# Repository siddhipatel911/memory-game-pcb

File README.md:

# Memory Game Revision - PCB Design

A custom ESP32-based memory game built on a hand-designed PCB.  
This is a learning project covering embedded firmware, schematic design, and PCB layout.

> **PCB prototype sponsored by [PCBWay](https://www.pcbway.com)**

---

## Project Status

| Stage | Status |
|-------|--------|
| Breadboard prototype | ✅ Complete |
| Hardware test firmware | ✅ Complete |
| KiCad schematic | ✅ Complete |
| PCB layout | ✅ Complete |
| PCB manufacturing | 🔄 In progress (PCBWay) |
| Final game logic firmware | ⏳ Planned |

---

## Related Project

This repository is a simplified hardware redesign of the original Delirium Memory Game project.

The original project focused on a more advanced **RGB** memory game system with expanded gameplay logic and additional hardware features.

This repository focuses specifically on:

- **ESP32** hardware prototyping
- KiCad **PCB** design
- breadboard testing
- **PCB** manufacturing preparation
- beginner-friendly embedded hardware development

Original project repository:

➡️ [https://github.com/siddhipatel911/Delirium-Memory-Game](https://github.com/siddhipatel911/Delirium-Memory-Game)

---

## Hardware Overview

- **Microcontroller:** ESP32-WROOM-32E dev board (removable via female socket headers)
- **Inputs:** 3 tactile pushbuttons (GPIO 21, 22, 23)
- **Outputs:** 3 LEDs with 220Ω current-limiting resistors (GPIO 25, 26, 27)
- **PCB:** Custom 2-layer board designed in KiCad 10, manufactured by PCBWay
- **Power:** USB via ESP32 dev board

### GPIO Mapping

| Component | GPIO |
|-----------|------|
| SW1 | 23 |
| SW2 | 22 |
| SW3 | 21 |
| D1 | 25 |
| D2 | 26 |
| D3 | 27 |

---

## PCB Design

Designed in **KiCad 10.0.0**. 2-layer FR4 board, 82.5 × 62.2mm.

- All through-hole components for beginner-friendly hand soldering
- Female socket headers allow the ESP32 dev board to remain removable and reusable
- F.Cu GND copper pour
- 4× M3 mounting holes at corners

### Schematic

### PCB Layout

### 3D Render

---

## Breadboard Prototype

Initial hardware validation was done on a breadboard before PCB design.

---

## Firmware

### Current: Hardware Test
Located in [`memory_game/firmware/hardware_test/`](memory_game/firmware/hardware_test/)

Tests button inputs and LED outputs — each button lights its corresponding LED when pressed.

### Planned: Game Logic
The final memory game firmware will be added to [`memory_game/firmware/game_logic/`](memory_game/firmware/game_logic/) after hardware is validated.

---

## Repository Structure

```text
memory-game-pcb/
└── memory_game/
    ├── firmware/
    │   ├── hardware_test/     # Current test firmware
    │   └── game_logic/        # Final game firmware (coming soon)
    ├── hardware/
    │   ├── kicad/             # KiCad schematic and PCB files
    │   └── gerbers/           # Gerber files for manufacturing
    ├── docs/
    │   └── images/            # Project photos and renders
    └── bom/
        └── bom.md             # Bill of materials
```

---

## Sponsor

PCB prototypes for this project are sponsored by **[PCBWay](https://www.pcbway.com)**.  
- PCBWay provides high-quality PCB manufacturing and assembly services for makers, hobbyists, and professionals.  
- I'll be sharing my honest review of the manufacturing quality and experience once the boards arrive.

---

## License

MIT License — see [LICENSE](LICENSE) for details.

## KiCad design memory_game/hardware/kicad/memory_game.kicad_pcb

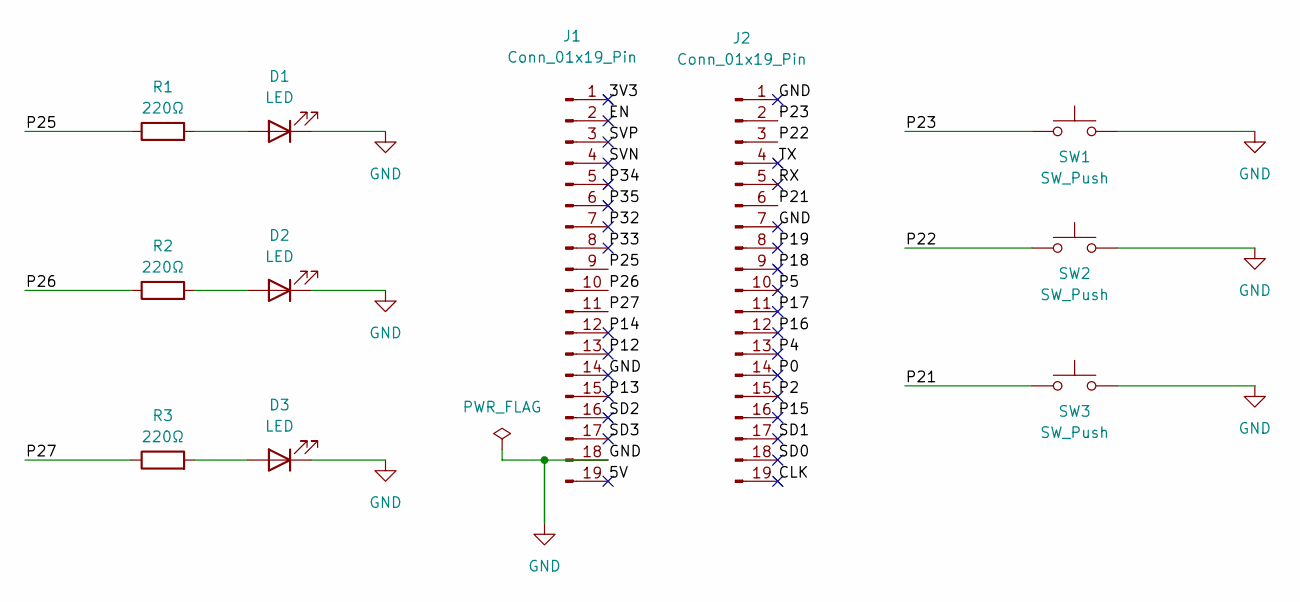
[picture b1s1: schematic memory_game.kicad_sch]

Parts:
D1, D2, D3: LED; LED_D5.0mm
J1, J2: Conn_01x19_Pin; PinSocket_1x19_P2.54mm_Vertical
R1, R2, R3: 220Ω; R_Axial_DIN0207_L6.3mm_D2.5mm_P7.62mm_Horizontal
SW1, SW2, SW3: SW_Push; SW_PUSH_6mm

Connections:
/3V3: J1.1
/5V: J1.19
/CLK: J2.19
/EN: J1.2
/P0: J2.14
/P2: J2.15
/P4: J2.13
/P5: J2.10
/P12: J1.13
/P13: J1.15
/P14: J1.12
/P15: J2.16
/P16: J2.12
/P17: J2.11
/P18: J2.9
/P19: J2.8
/P21: J2.6, SW3.1
/P22: J2.3, SW2.1
/P23: J2.2, SW1.1
/P25: J1.9, R1.1
/P26: J1.10, R2.1
/P27: J1.11, R3.1
/P32: J1.7
/P33: J1.8
/P34: J1.5
/P35: J1.6
/RX: J2.5
/SD0: J2.18
/SD1: J2.17
/SD2: J1.16
/SD3: J1.17
/SVN: J1.4
/SVP: J1.3
/TX: J2.4
GND: D1.1 (K), D2.1 (K), D3.1 (K), J1.14, J1.18, J2.1, J2.7, SW1.2, SW2.2, SW3.2
unnamed: D1.2 (A), R1.2
unnamed: D2.2 (A), R2.2
unnamed: D3.2 (A), R3.2

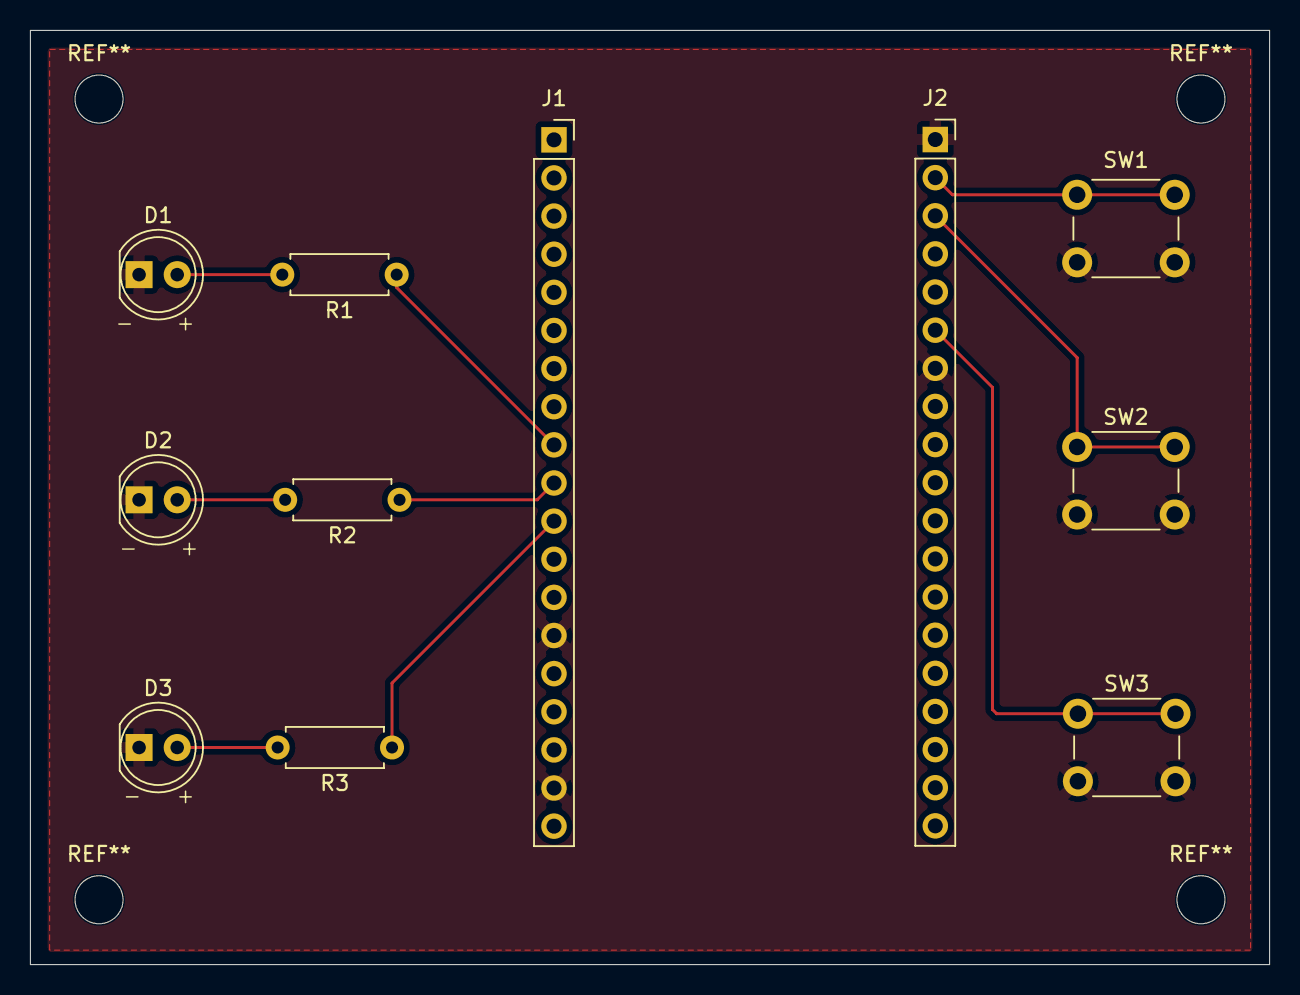
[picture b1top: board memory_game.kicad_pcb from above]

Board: 2 copper layers, 82.5 x 62.2 mm, 11 parts (0 on the bottom side), 10 nets.

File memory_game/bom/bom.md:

# Bill of Materials — Revised Memory Game

| Reference | Component | Value | Footprint | Quantity |
|-----------|-----------|-------|-----------|----------|
| U1 | ESP32-WROOM-32E Dev Board | — | Female Socket Header 1×19 ×2 | 1 |
| R1, R2, R3 | Resistor | 220Ω | Axial THT | 3 |
| D1, D2, D3 | LED | Red, 5mm | LED_D5.0mm THT | 3 |
| SW1, SW2, SW3 | Tactile Pushbutton | 6mm | SW_PUSH_6mm THT | 3 |
| J1, J2 | Female Socket Header | 1×19 2.54mm | PinSocket_1x19 | 2 |
| MH1–MH4 | Mounting Hole | M3 | MountingHole_3.2mm_M3 | 4 |

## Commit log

2026-05-16 Initialize Repo
2026-05-16 Add project images
    Add images for the schematic, PCB layout, 3D render, breadboard prototype.
2026-05-16 Add Bill of Materials for revised memory game
2026-05-16 Revise README
    Updated file paths and project details in README.
2026-05-16 Add breadboard prototype image
2026-05-16 Document related project and its features
    Added a section about the related project and its focus areas.
